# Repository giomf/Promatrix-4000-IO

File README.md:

# Promatix-4000-IO

8-output / 7-input digital IO board (RP2040-based) with USB serial control.

* `PCB/` – KiCad hardware design.
* `promatrix-firmware/` – Rust firmware (Embassy), see `promatrix-firmware/README.md`.
* `promatrix-protocol/` – wire protocol shared between firmware and `promatrix-io`.
* `promatrix-io/` – host-side Rust library + `promatrix-io` CLI, see `promatrix-io/README.md`.

Enter the Nix dev shell (`nix develop`) for the pinned toolchain and tools
used by all three Rust crates.

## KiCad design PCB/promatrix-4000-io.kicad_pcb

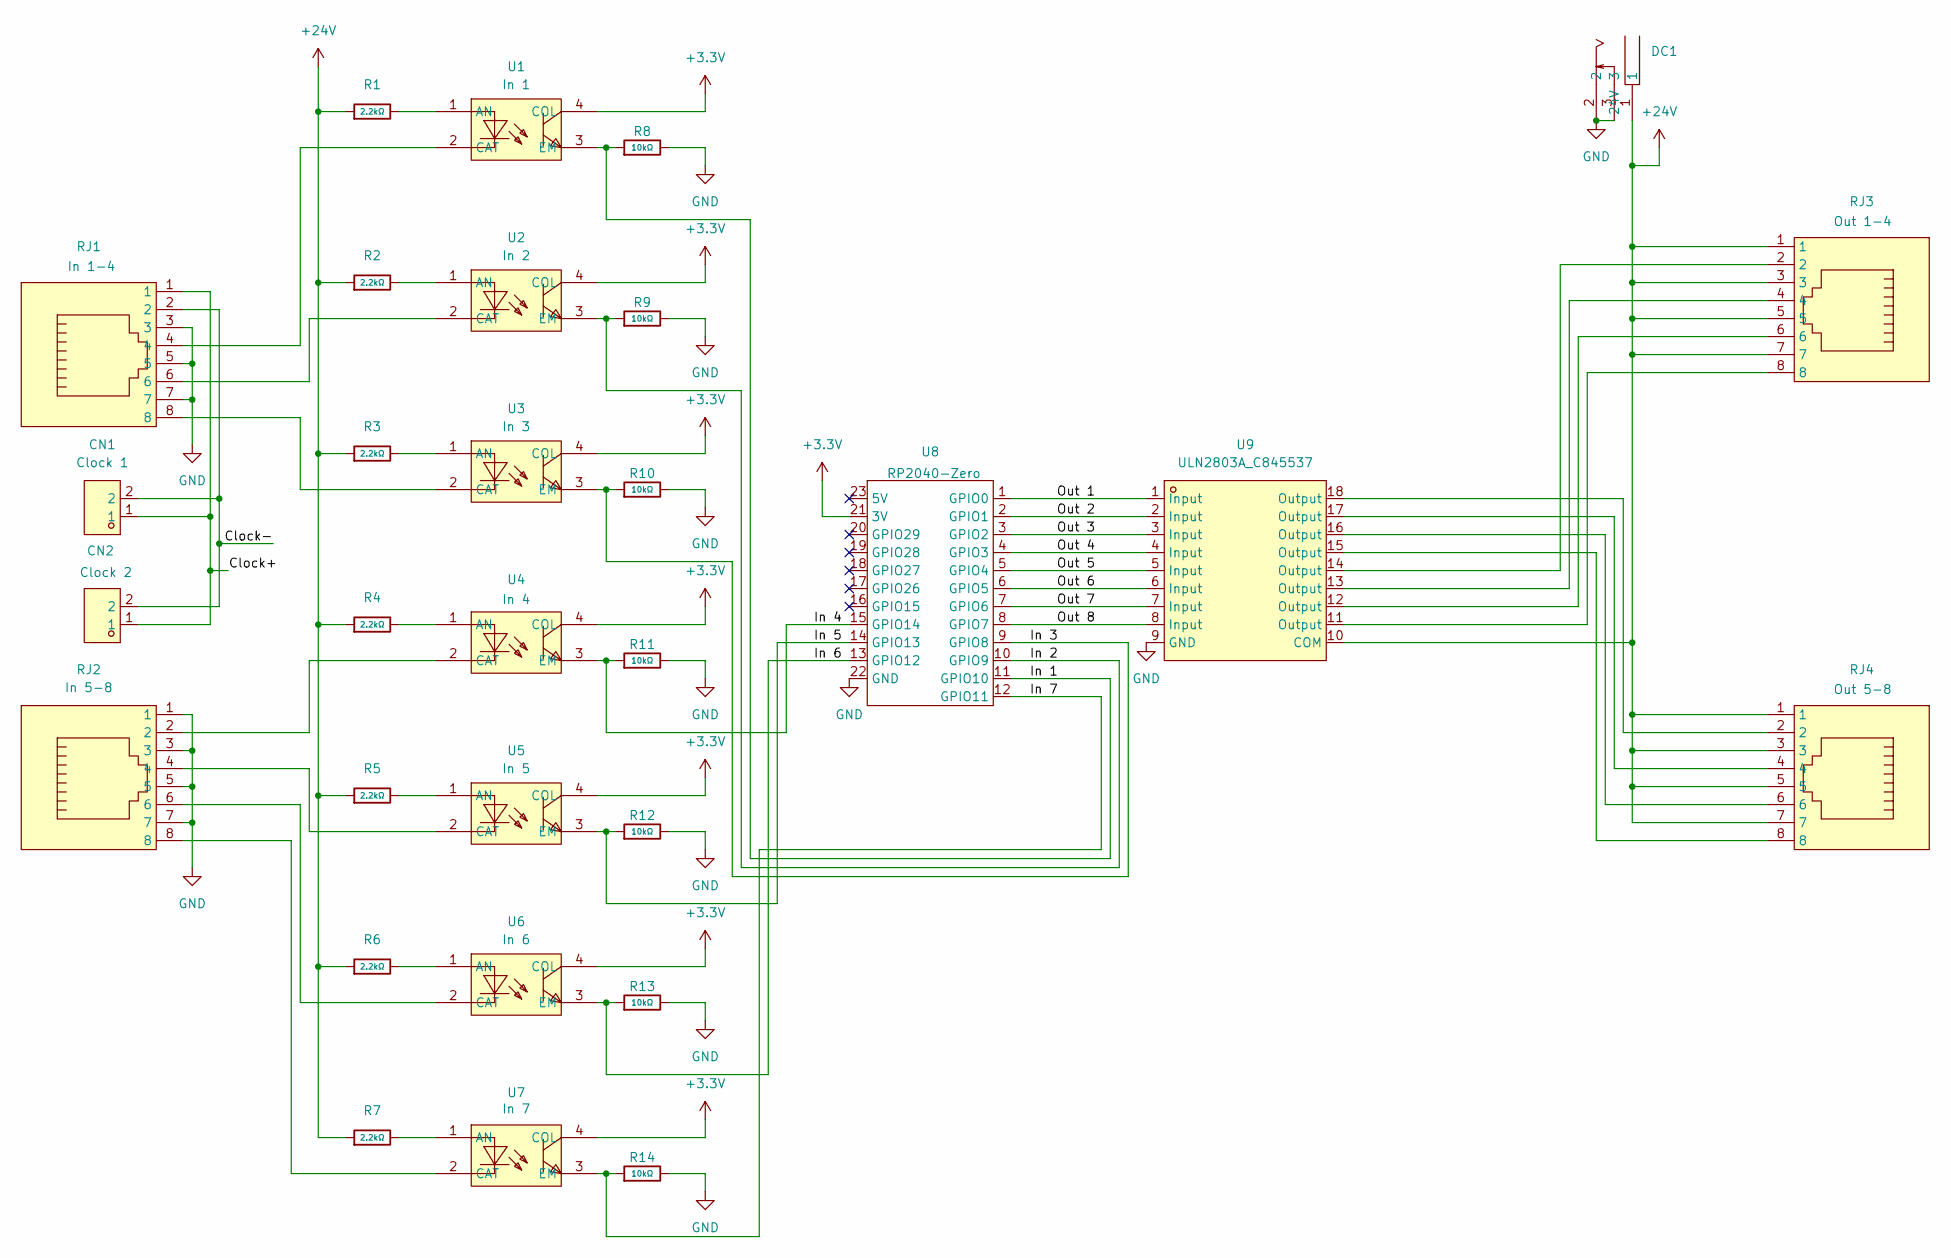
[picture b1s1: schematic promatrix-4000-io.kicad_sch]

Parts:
CN1, CN2: JL127-50002G01; CONN-TH_2P-P5.08_JL127-50002G01; MPN JL127-50002G01; LCSC Part C387826
DC1: DC050-T; DC-IN_DC050-T; LCSC Part C431534
R1, R2, R3, R4, R5, R6, R7: 2.2kΩ; R_0402; Overload Voltage (Max) 50V; Tolerance ±1%; Part 0402WGF2201TCE; LCSC C25879
R8, R9, R10, R11, R12, R13, R14: 10kΩ; R_0402; Overload Voltage (Max) 50V; Tolerance ±1%; Part 0402WGF1002TCE; LCSC C25744
RJ1, RJ2, RJ3, RJ4: R-RJ45R08P-A004; RJ45-TH_R-RJ45R08P-A004; MPN R-RJ45R08P-A004; LCSC Part C385834
U1, U2, U3, U4, U5, U6, U7: PC817X3CSP9F; OPTO-SMD-4_L4.6-W6.5-P2.54-LS10.3-TL; MPN PC817X3CSP9F; LCSC Part C41807
U8: rp2040-zero
U9: ULN2803A_C845537; SOP-18_L11.4-W7.6-P1.27-LS10.6-BL; MPN ULN2803A; LCSC Part C845537

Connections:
+3.3V: U1.4 (COL), U2.4 (COL), U3.4 (COL), U4.4 (COL), U5.4 (COL), U6.4 (COL), U7.4 (COL), U8.21 (3V)
+24V: DC1.1, R1.1, R2.1, R3.1, R4.1, R5.1, R6.1, R7.1, RJ3.1, RJ3.3, RJ3.5, RJ3.7, RJ4.1, RJ4.3, RJ4.5, RJ4.7, U9.10 (COM)
/Clock+: CN1.1, CN2.1, RJ1.1
/Clock-: CN1.2, CN2.2, RJ1.2
/In 1: R8.1, U1.3 (EM), U8.11 (GPIO10)
/In 2: R9.1, U2.3 (EM), U8.10 (GPIO9)
/In 3: R10.1, U3.3 (EM), U8.9 (GPIO8)
/In 4: R11.1, U4.3 (EM), U8.15 (GPIO14)
/In 5: R12.1, U5.3 (EM), U8.14 (GPIO13)
/In 6: R13.1, U6.3 (EM), U8.13 (GPIO12)
/In 7: R14.1, U7.3 (EM), U8.12 (GPIO11)
/Out 1: U8.1 (GPIO0), U9.1 (Input)
/Out 2: U8.2 (GPIO1), U9.2 (Input)
/Out 3: U8.3 (GPIO2), U9.3 (Input)
/Out 4: U8.4 (GPIO3), U9.4 (Input)
/Out 5: U8.5 (GPIO4), U9.5 (Input)
/Out 6: U8.6 (GPIO5), U9.6 (Input)
/Out 7: U8.7 (GPIO6), U9.7 (Input)
/Out 8: U8.8 (GPIO7), U9.8 (Input)
GND: DC1.2, DC1.3, R8.2, R9.2, R10.2, R11.2, R12.2, R13.2, R14.2, RJ1.3, RJ1.5, RJ1.7, RJ2.1, RJ2.3, RJ2.5, RJ2.7, U8.22 (GND), U9.9 (GND)
unnamed: RJ3.2, U9.14 (Output)
unnamed: RJ3.4, U9.13 (Output)
unnamed: RJ3.6, U9.12 (Output)
unnamed: RJ3.8, U9.11 (Output)
unnamed: RJ4.2, U9.18 (Output)
unnamed: RJ4.4, U9.17 (Output)
unnamed: RJ4.6, U9.16 (Output)
unnamed: RJ4.8, U9.15 (Output)
unnamed: R1.2, U1.1 (AN)
unnamed: RJ1.4, U1.2 (CAT)
unnamed: R2.2, U2.1 (AN)
unnamed: RJ1.6, U2.2 (CAT)
unnamed: R3.2, U3.1 (AN)
unnamed: RJ1.8, U3.2 (CAT)
unnamed: R4.2, U4.1 (AN)
unnamed: RJ2.2, U4.2 (CAT)
unnamed: R5.2, U5.1 (AN)
unnamed: RJ2.4, U5.2 (CAT)
unnamed: R6.2, U6.1 (AN)
unnamed: RJ2.6, U6.2 (CAT)
unnamed: R7.2, U7.1 (AN)
unnamed: RJ2.8, U7.2 (CAT)

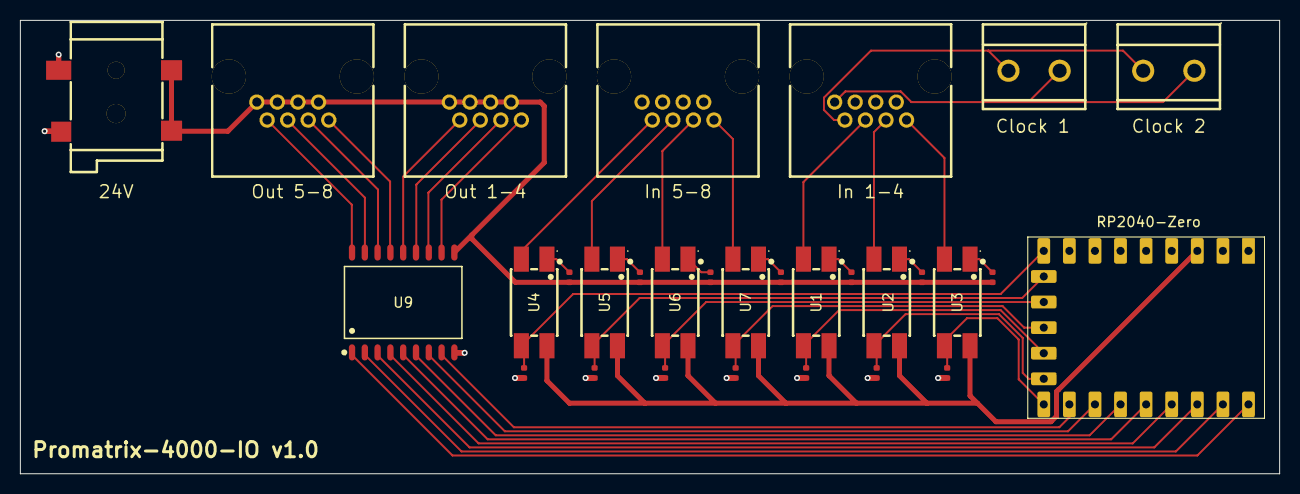
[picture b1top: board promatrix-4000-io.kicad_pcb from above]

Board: 2 copper layers, 125.0 x 45.0 mm, 30 parts (0 on the bottom side), 42 nets.

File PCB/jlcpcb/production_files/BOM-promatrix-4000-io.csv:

Comment,Designator,Footprint,LCSC,Quantity
10kΩ,"R10,R11,R12,R13,R14,R8,R9",R_0402,C25744,7
2.2kΩ,"R1,R2,R3,R4,R5,R6,R7",R_0402,C25879,7
DC050-T,DC1,DC-IN_DC050-T,C431534,1
JL127-50002G01,"CN1,CN2",CONN-TH_2P-P5.08_JL127-50002G01,C387826,2
PC817X3CSP9F,"U1,U2,U3,U4,U5,U6,U7",OPTO-SMD-4_L4.6-W6.5-P2.54-LS10.3-TL,C41807,7
R-RJ45R08P-A004,"RJ1,RJ2,RJ3,RJ4",RJ45-TH_R-RJ45R08P-A004,C385834,4
ULN2803A_C845537,U9,SOP-18_L11.4-W7.6-P1.27-LS10.6-BL,C845537,1
~,U8,rp2040-zero,,1

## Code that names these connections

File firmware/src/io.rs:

//! GPIO pin mapping between logical IO channels and physical RP2040 pins.
//!
//! ## Outputs
//!
//! Driven through a ULN2803A Darlington array, sinking the attached load to
//! GND (the load itself is referenced to +24V). Logical channels `Out1..=Out4`
//! map to `GPIO4..=GPIO7` and `Out5..=Out8` to `GPIO0..=GPIO3` (matching the
//! PCB silkscreen). The level is inverted: logical "on" == GPIO low, so all
//! outputs start high (off).
//!
//! ## Inputs
//!
//! Sensed through PC817 optocouplers. Measured on the board, idle inputs
//! read low, so the level is not inverted: logical/reported `1` == input
//! active == electrical high.
//!
//! Only 7 of the 8 input channels are wired as inputs; `In1` is the clock
//! and therefore not exposed here. The remaining channels are
//! wired to GPIOs out of numerical order:
//!
//! | Logical channel | GPIO |
//! |------------------|------|
//! | In2              | 10   |
//! | In3              | 9    |
//! | In4              | 8    |
//! | In5              | 14   |
//! | In6              | 13   |
//! | In7              | 12   |
//! | In8              | 11   |

use embassy_rp::Peri;
use embassy_rp::gpio::{Input, Level, Output, Pull};
use embassy_rp::peripherals::{
    PIN_0, PIN_1, PIN_2, PIN_3, PIN_4, PIN_5, PIN_6, PIN_7, PIN_8, PIN_9, PIN_10, PIN_11, PIN_12,
    PIN_13, PIN_14,
};

/// Number of digital outputs/inputs, re-exported from the shared wire
/// protocol crate since it also defines the `STATUS` bitmask widths.
pub use protocol::{NUM_INPUTS, NUM_OUTPUTS};

/// Physical pins required to build [`Outputs`], in `Out1..=Out8` order.
pub struct OutputPins {
    pub out1: Peri<'static, PIN_4>,
    pub out2: Peri<'static, PIN_5>,
    pub out3: Peri<'static, PIN_6>,
    pub out4: Peri<'static, PIN_7>,
    pub out5: Peri<'static, PIN_0>,
    pub out6: Peri<'static, PIN_1>,
    pub out7: Peri<'static, PIN_2>,
    pub out8: Peri<'static, PIN_3>,
}

/// Physical pins required to build [`Inputs`], in `In2..=In8` order.
pub struct InputPins {
    pub in2: Peri<'static, PIN_10>,
    pub in3: Peri<'static, PIN_9>,
    pub in4: Peri<'static, PIN_8>,
    pub in5: Peri<'static, PIN_14>,
    pub in6: Peri<'static, PIN_13>,
    pub in7: Peri<'static, PIN_12>,
    pub in8: Peri<'static, PIN_11>,
}

/// All 8 digital outputs, indexed by logical channel (index 0 == `Out1`).
pub struct Outputs(pub [Output<'static>; NUM_OUTPUTS]);

impl Outputs {
    pub fn new(pins: OutputPins) -> Self {
        Self([
            Output::new(pins.out1, Level::High),
            Output::new(pins.out2, Level::High),
            Output::new(pins.out3, Level::High),
            Output::new(pins.out4, Level::High),
            Output::new(pins.out5, Level::High),
            Output::new(pins.out6, Level::High),
            Output::new(pins.out7, Level::High),
            Output::new(pins.out8, Level::High),
        ])
    }

    /// Set output `output` (board label number, `1..=8`) to `on`.
    ///
    /// Silently ignores out-of-range outputs.
    pub fn set(&mut self, output: u8, on: bool) {
        if let Some(pin) = self.0.get_mut((output as usize).wrapping_sub(1)) {
            pin.set_level(if on { Level::Low } else { Level::High });
        }
    }
}

/// The 7 wired digital inputs, indexed by logical channel (index 0 == `In2`).
pub struct Inputs(pub [Input<'static>; NUM_INPUTS]);

impl Inputs {
    pub fn new(pins: InputPins) -> Self {
        // NOTE: idle inputs measured low despite this pull-up; if an
        // unconnected input reads "on", switch to `Pull::Down`.
        Self([
            Input::new(pins.in2, Pull::Up),
            Input::new(pins.in3, Pull::Up),
            Input::new(pins.in4, Pull::Up),
            Input::new(pins.in5, Pull::Up),
            Input::new(pins.in6, Pull::Up),
            Input::new(pins.in7, Pull::Up),
            Input::new(pins.in8, Pull::Up),
        ])
    }
}

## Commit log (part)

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2026-06-22 Add PCB
